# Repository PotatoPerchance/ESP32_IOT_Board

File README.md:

# ESP IoT Board

Custom-built 4-layer PCB IoT development board featuring onboard sensors for weather, ambient light, and audio processing, along with display support and integrated Wi-Fi/Bluetooth capabilities.

---

## Features

* **Sensors**: Temperature, humidity, pressure (BME280), and ambient light sensing.
* **Audio**: Microphone input with MAX4466EXK amplifier circuit.
* **Connectivity**: Integrated Wi-Fi and Bluetooth via ESP32-C3.
* **Power & Charging**: Onboard LiPo battery charger circuit (MCP73871) with USB power path management.
* **Storage & Expansion**: External Flash memory (W25Q32JVSSIQ) and MicroSD card slot.
* **Display Support**: Display header interface for external screens.
* **Interface**: USB Serial communication and power/charging over USB.

---

## Motivation

I designed this to gain hands-on experience in 4-layer PCB design for complex and high-density PCBS.

---

## PCB Layout

### Signal Layers (F.Cu & B.Cu)

### Power & Ground Planes (In1.Cu & In2.Cu)

---

## Project Directory Structure

| Path / File | Description |
| :--- | :--- |
| `3D models/` | 3D models for components|
| `Footprints/` | KiCad footprints used in the project |
| `Pictures/` | Image assets and PCB screenshots|
| `production/` | Production files (Gerbers, drill files, assembly outputs) |
| `Symbols/` | Custom KiCad schematic symbol library |
| `ESP IOT dev board.kicad_pcb` | Main KiCad PCB layout file |
| `ESP IOT dev board.kicad_sch` | Root schematic file |
| `esp32.kicad_sch` | ESP32-C3 microcontroller schematic sheet |
| `sensors.kicad_sch` | Environmental and audio sensor schematic sheet |
| `user_interface.kicad_sch` | Display and user interface schematic sheet |
| `README.md` | Project documentation |

---

## Bill of Materials (BOM)
| Component | Description | Est. Unit Cost (USD) |
| :--- | :--- | :--- |
| **ESP32-C3-WROOM-02** | Wi-Fi & BLE Microcontroller Module | ~$4.00 |
| **BME280** | Temperature, Humidity, & Pressure Sensor | ~$2.50 |
| **Light Sensor (LDR / Phototransistor)** | Ambient Light Sensing | ~$0.40 |
| **MAX4466EXK+T** | Low-Noise Microphone Amplifier IC | ~$1.20 |
| **Electret Condenser Microphone** | 2-pin Audio Input | ~$1 |
| **Winbond W25Q32JVSSIQ** | 32M-bit (4MB) SPI Flash Memory | ~$0.50 |
| **MCP73871** | LiPo Battery Charger & Power Path Management IC | ~$1.80 |
| **MicroSD Card Holder** | Push-Push / Push-Pull Socket | ~$1 |
| **USB Type-C Connector** | 16-pin / 24-pin Surface Mount Connector | ~$0.35 |
| **LiPo Battery** | 3.7V Single Cell Lithium-Polymer Battery | ~$3.50 |
| **Miscellaneous Components** | Resistors, Capacitors, LEDs, LDO, Connectors | ~$5.00 |
| **PCB Manufacturing** | Custom 4-Layer PCB Fabrication | ~$8.00 |
| **Shipping Fees** | Component & PCB Shipping | ~$15.00 |
| **Total Estimated Cost** | *(Including Fabrication & Shipping)* | **~$45** |

---

~ built with love ❤️

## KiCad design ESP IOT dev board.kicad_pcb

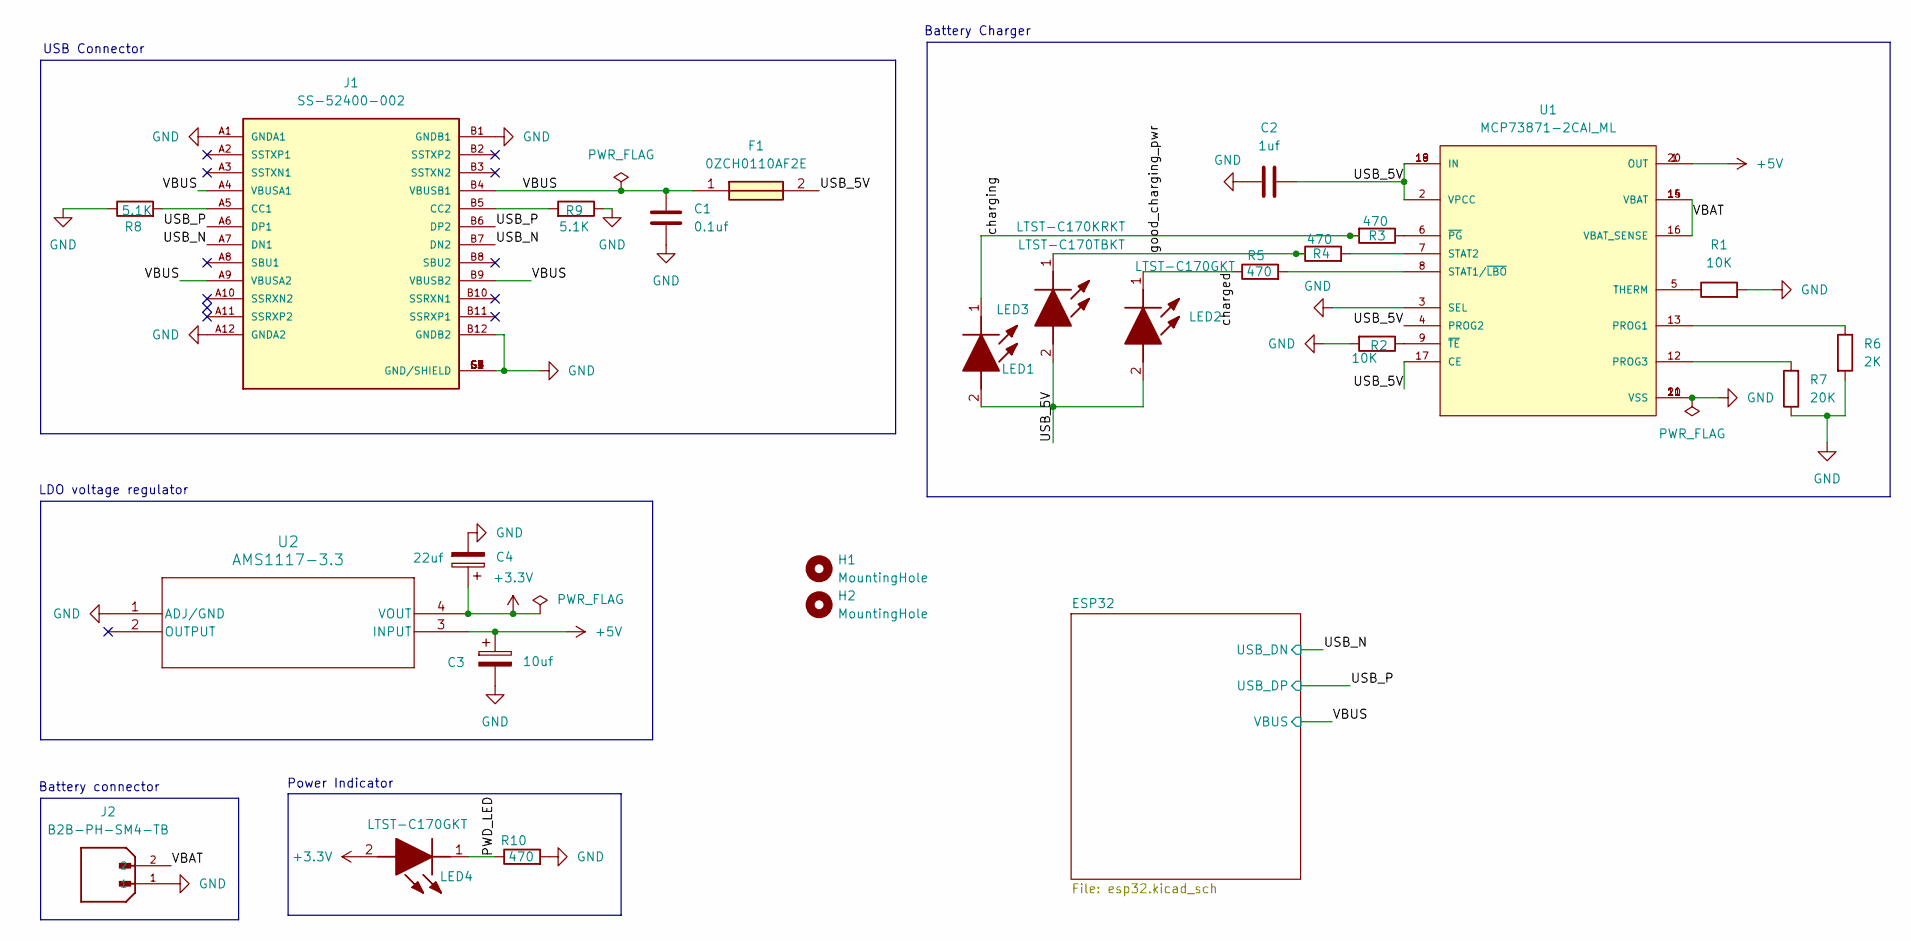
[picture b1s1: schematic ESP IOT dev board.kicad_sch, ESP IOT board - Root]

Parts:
C1: 0.1uf; C_0805_2012Metric_Pad1.18x1.45mm_HandSolder
C2: 1uf; C_0805_2012Metric_Pad1.18x1.45mm_HandSolder
C3: 10uf; CP_EIA-6032-28_Kemet-C_HandSolder
C4: 22uf; CP_EIA-6032-28_Kemet-C_HandSolder
F1: 0ZCH0110AF2E; FUSC3226X100N; Manufacturer_Part_Number 0ZCH0110AF2E
H1, H2: MountingHole; MountingHole_2.5mm
J1: SS-52400-002; BELFUSE_SS-52400-002; PARTREV A0
J2: B2B-PH-SM4-TB; JST_B2B-PH-SM4-TB; PARTREV N/A
LED1: LTST-C170KRKT; LEDC2012X120N; Manufacturer_Part_Number LTST-C170KRKT; Mouser Part Number 859-LTST-C170KRKT
LED2, LED4: LTST-C170GKT; LEDC2012X120N; Manufacturer_Part_Number LTST-C170GKT; Mouser Part Number 859-LTST-C170GKT
LED3: LTST-C170TBKT; LEDC2012X120N; Manufacturer_Part_Number LTST-C170TBKT; Mouser Part Number 859-LTST-C170TBKT
R1, R2: 10K; R_0805_2012Metric_Pad1.20x1.40mm_HandSolder
R3, R4, R5, R10: 470; R_0805_2012Metric_Pad1.20x1.40mm_HandSolder
R6: 2K; R_0805_2012Metric_Pad1.20x1.40mm_HandSolder
R7: 20K; R_0805_2012Metric_Pad1.20x1.40mm_HandSolder
R8, R9: 5.1K; R_0805_2012Metric_Pad1.20x1.40mm_HandSolder
U1: MCP73871-2CAI_ML; QFN50P400X400X100-21N; PARTREV D
U2: AMS1117-3.3; SOT_AMS1117-2.5_AMS

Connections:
+3.3V: C4.1, LED4.2 (A), U2.4 (VOUT); also elsewhere on the board
+5V: C3.1, U1.1 (OUT), U1.20 (OUT), U2.3 (INPUT)
/PWD_LED: LED4.1 (K), R10.1; also elsewhere on the board
/USB_5V: C2.2, F1.2, LED1.2 (A), LED2.2 (A), LED3.2 (A), U1.2 (VPCC), U1.4 (PROG2), U1.17 (CE), U1.18 (IN), U1.19 (IN); also elsewhere on the board
/USB_N: J1.A7 (DN1), J1.B7 (DN2); also elsewhere on the board
/USB_P: J1.A6 (DP1), J1.B6 (DP2); also elsewhere on the board
/VBAT: J2.2, U1.14 (VBAT), U1.15 (VBAT), U1.16 (VBAT_SENSE)
/VBUS: C1.1, F1.1, J1.A4 (VBUSA1), J1.A9 (VBUSA2), J1.B4 (VBUSB1), J1.B9 (VBUSB2); also elsewhere on the board
/charged: LED2.1 (K), R5.1; also elsewhere on the board
/charging: LED1.1 (K), R3.2; also elsewhere on the board
/good_charging_pwr: LED3.1 (K), R4.1; also elsewhere on the board
unnamed: J1.A5 (CC1), R8.2
unnamed: R6.1, U1.13 (PROG1)
unnamed: R7.2, U1.12 (PROG3)
unnamed: R5.2, U1.8 (STAT1/~LBO)
unnamed: R4.2, U1.7 (STAT2)
unnamed: R1.1, U1.5 (THERM)
unnamed: R3.1, U1.6 (~PG)
unnamed: R2.1, U1.9 (~TE)

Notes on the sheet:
LDO voltage regulator
Battery Charger
USB Connector
Battery connector
Power Indicator

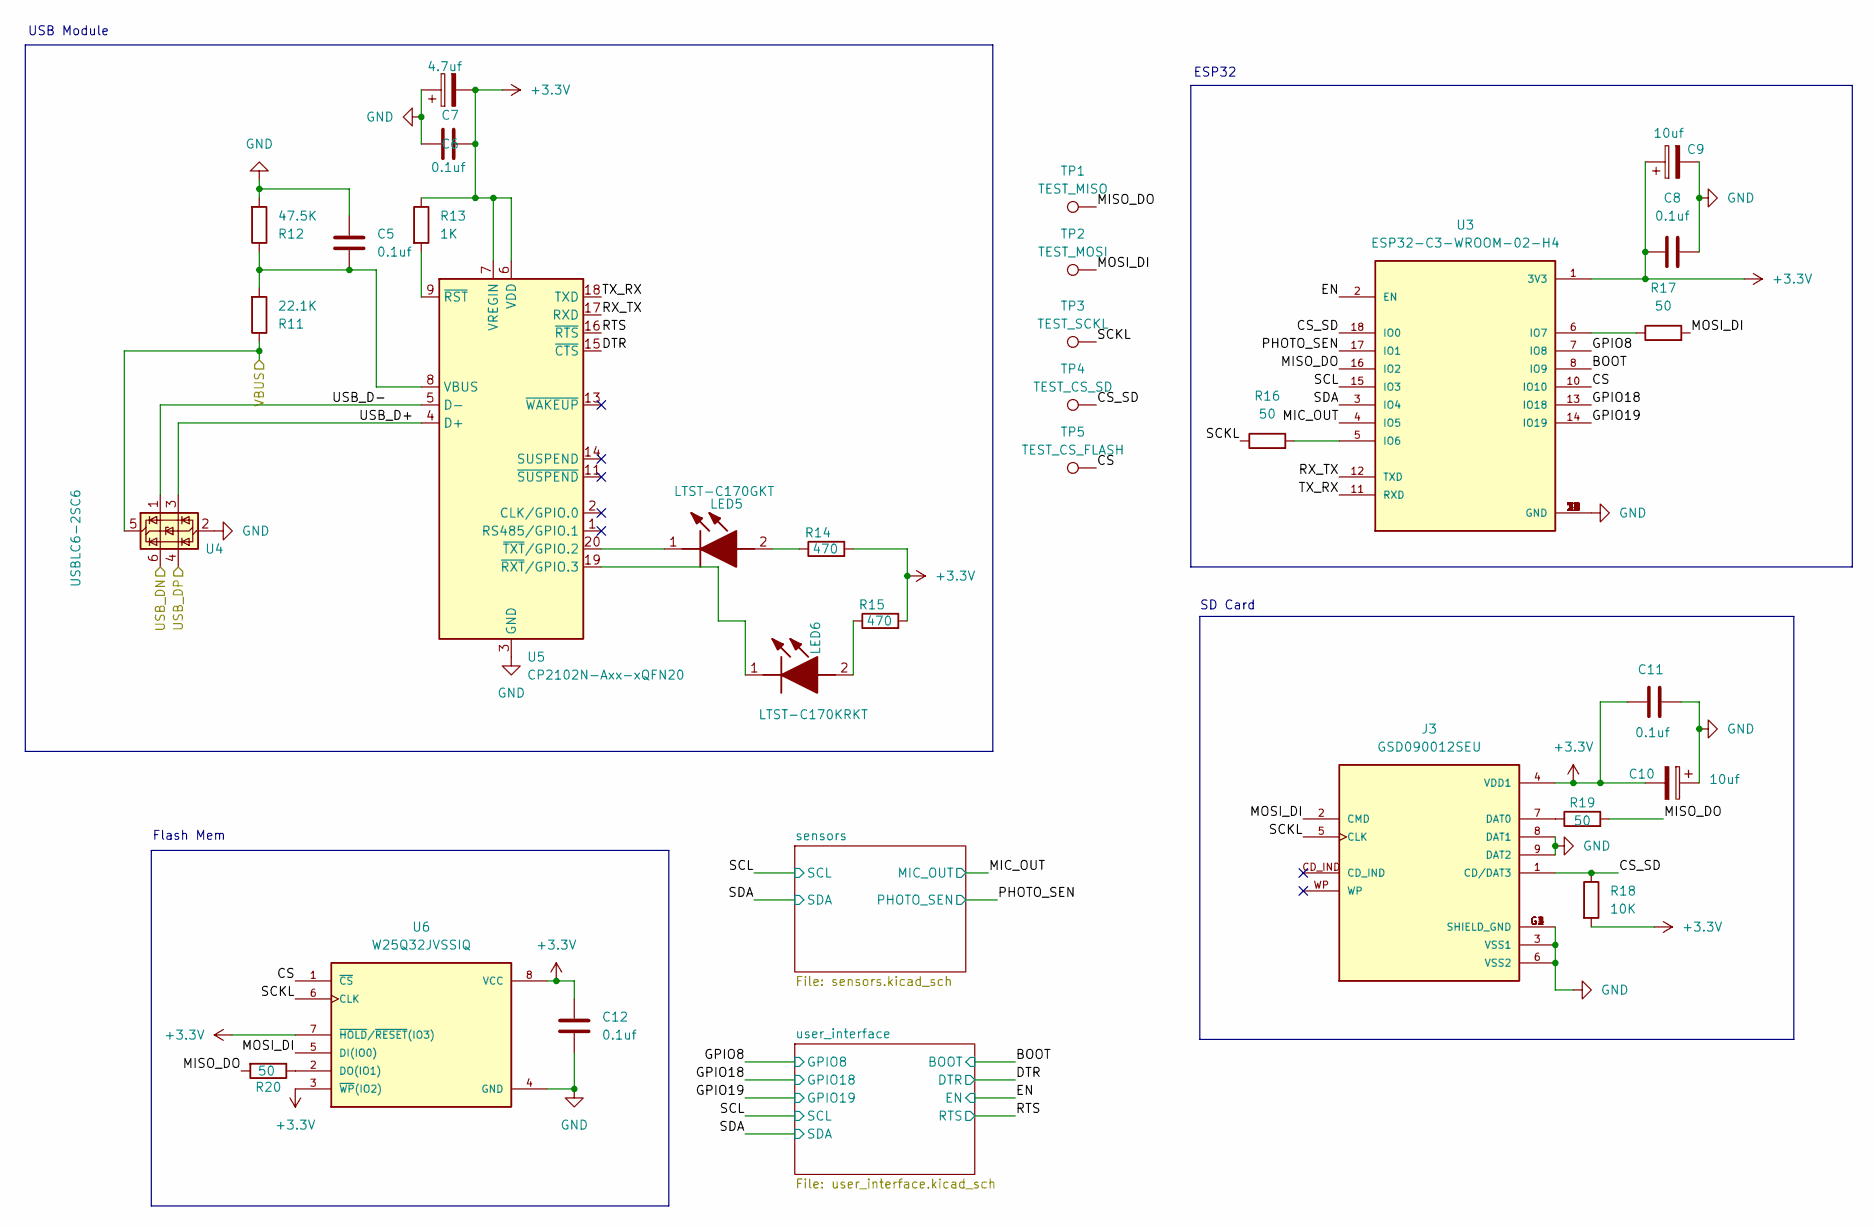
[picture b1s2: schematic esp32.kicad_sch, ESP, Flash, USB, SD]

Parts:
C5, C6, C8, C11, C12: 0.1uf; C_0805_2012Metric_Pad1.18x1.45mm_HandSolder
C7: 4.7uf; CP_EIA-6032-28_Kemet-C_HandSolder
C9, C10: 10uf; CP_EIA-6032-28_Kemet-C_HandSolder
J3: GSD090012SEU; AMPHENOL_GSD090012SEU; PARTREV E
LED5: LTST-C170GKT; LEDC2012X120N; Manufacturer_Part_Number LTST-C170GKT; Mouser Part Number 859-LTST-C170GKT
LED6: LTST-C170KRKT; LEDC2012X120N; Manufacturer_Part_Number LTST-C170KRKT; Mouser Part Number 859-LTST-C170KRKT
R11: 22.1K; R_0805_2012Metric_Pad1.20x1.40mm_HandSolder
R12: 47.5K; R_0805_2012Metric_Pad1.20x1.40mm_HandSolder
R13: 1K; R_0805_2012Metric_Pad1.20x1.40mm_HandSolder
R14, R15: 470; R_0805_2012Metric_Pad1.20x1.40mm_HandSolder
R16, R17, R19, R20: 50; R_0805_2012Metric_Pad1.20x1.40mm_HandSolder
R18: 10K; R_0805_2012Metric_Pad1.20x1.40mm_HandSolder
TP1: TEST_MISO; TestPoint_Pad_D1.0mm
TP2: TEST_MOSI; TestPoint_Pad_D1.0mm
TP3: TEST_SCKL; TestPoint_Pad_D1.0mm
TP4: TEST_CS_SD; TestPoint_Pad_D1.0mm
TP5: TEST_CS_FLASH; TestPoint_Pad_D1.0mm
U3: ESP32-C3-WROOM-02-H4; MODULE_ESP32-C3-WROOM-02-H4
U4: USBLC6-2SC6; SOT-23-6
U5: CP2102N-Axx-xQFN20; SiliconLabs_QFN-20-1EP_3x3mm_P0.5mm_EP1.8x1.8mm
U6: W25Q32JVSSIQ; SOIC127P790X216-8N; M_PART_NUMBER W25QXX

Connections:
+3.3V: C6.2, C7.2, C8.1, C9.1, C10.2, C11.2, C12.2, J3.4 (VDD1), R13.1, R14.2, R15.2, R18.2, U3.1 (3V3), U5.6 (VDD), U5.7 (VREGIN), U6.3 (~WP(IO2)), U6.7 (~HOLD/~RESET(IO3)), U6.8 (VCC); also elsewhere on the board
/ESP32/BOOT: U3.8 (IO9); also elsewhere on the board
/ESP32/CS: TP5.1 (1_1), U3.10 (IO10), U6.1 (~CS)
/ESP32/CS_SD: J3.1 (CD/DAT3), R18.1, TP4.1 (1_1), U3.18 (IO0)
/ESP32/DTR: U5.15 (~CTS); also elsewhere on the board
/ESP32/EN: U3.2 (EN); also elsewhere on the board
/ESP32/GPIO8: U3.7 (IO8); also elsewhere on the board
/ESP32/GPIO18: U3.13 (IO18); also elsewhere on the board
/ESP32/GPIO19: U3.14 (IO19); also elsewhere on the board
/ESP32/MIC_OUT: U3.4 (IO5); also elsewhere on the board
/ESP32/MISO_DO: R19.2, R20.2, TP1.1 (1_1), U3.16 (IO2)
/ESP32/MOSI_DI: J3.2 (CMD), R17.2, TP2.1 (1_1), U6.5 (DI(IO0))
/ESP32/PHOTO_SEN: U3.17 (IO1); also elsewhere on the board
/ESP32/RTS: U5.16 (~RTS); also elsewhere on the board
/ESP32/RX_TX: U3.12 (TXD), U5.17 (RXD)
/ESP32/SCKL: J3.5 (CLK), R16.1, TP3.1 (1_1), U6.6 (CLK)
/ESP32/SCL: U3.15 (IO3); also elsewhere on the board
/ESP32/SDA: U3.3 (IO4); also elsewhere on the board
/ESP32/TX_RX: U3.11 (RXD), U5.18 (TXD)
/ESP32/USB_D+: U4.3 (I/O2), U5.4 (D+)
/ESP32/USB_D-: U4.1 (I/O1), U5.5 (D-)
/USB_N: U4.6 (I/O1); also elsewhere on the board
/USB_P: U4.4 (I/O2); also elsewhere on the board
/VBUS: R11.1, U4.5 (VBUS); also elsewhere on the board
unnamed: J3.7 (DAT0), R19.1
unnamed: LED5.2 (A), R14.1
unnamed: LED5.1 (K), U5.20 (~TXT/GPIO.2)
unnamed: LED6.2 (A), R15.1
unnamed: LED6.1 (K), U5.19 (~RXT/GPIO.3)
unnamed: R16.2, U3.5 (IO6)
unnamed: R17.1, U3.6 (IO7)
unnamed: C5.2, R11.2, R12.1, U5.8 (VBUS)
unnamed: R13.2, U5.9 (~RST)
unnamed: R20.1, U6.2 (DO(IO1))

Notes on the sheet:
Flash Mem
SD Card
ESP32
USB Module

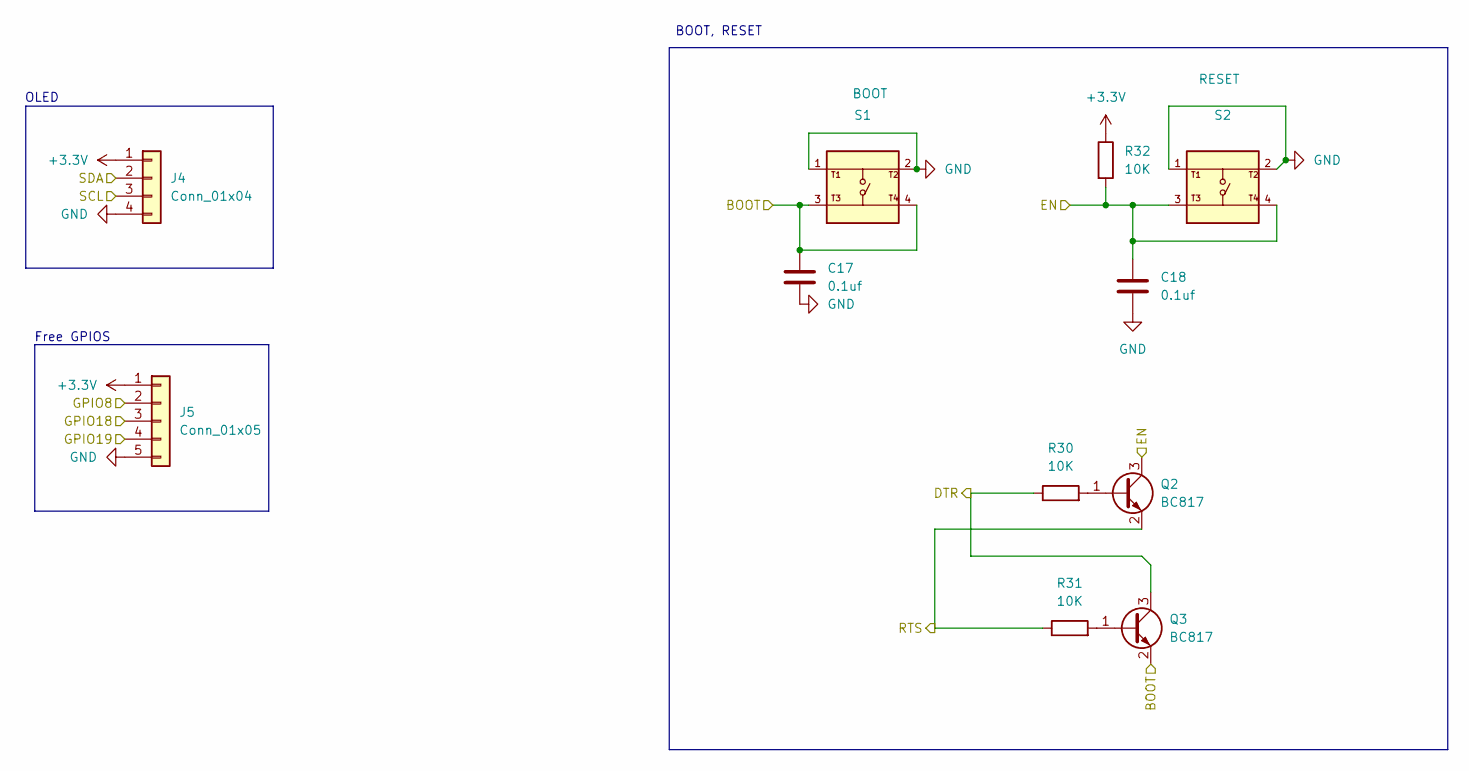
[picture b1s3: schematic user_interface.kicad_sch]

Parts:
C17, C18: 0.1uf; C_0805_2012Metric_Pad1.18x1.45mm_HandSolder
J4: Conn_01x04; PinHeader_1x04_P2.54mm_Vertical
J5: Conn_01x05; PinHeader_1x05_P2.54mm_Vertical
Q2, Q3: BC817; SOT-23
R30, R31, R32: 10K; R_0805_2012Metric_Pad1.20x1.40mm_HandSolder
S1: BOOT; SW_USLPT2819DT2TR; PARTREV P
S2: RESET; SW_USLPT2819DT2TR; PARTREV P

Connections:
+3.3V: J4.1, J5.1, R32.1; also elsewhere on the board
/ESP32/BOOT: C17.1, Q3.2 (E), S1.3, S1.4; also elsewhere on the board
/ESP32/DTR: Q3.3 (C), R30.1; also elsewhere on the board
/ESP32/EN: C18.1, Q2.3 (C), R32.2, S2.3, S2.4; also elsewhere on the board
/ESP32/GPIO8: J5.2; also elsewhere on the board
/ESP32/GPIO18: J5.3; also elsewhere on the board
/ESP32/GPIO19: J5.4; also elsewhere on the board
/ESP32/RTS: Q2.2 (E), R31.1; also elsewhere on the board
/ESP32/SCL: J4.3; also elsewhere on the board
/ESP32/SDA: J4.2; also elsewhere on the board
unnamed: Q2.1 (B), R30.2
unnamed: Q3.1 (B), R31.2

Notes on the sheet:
BOOT, RESET
Free GPIOS
OLED

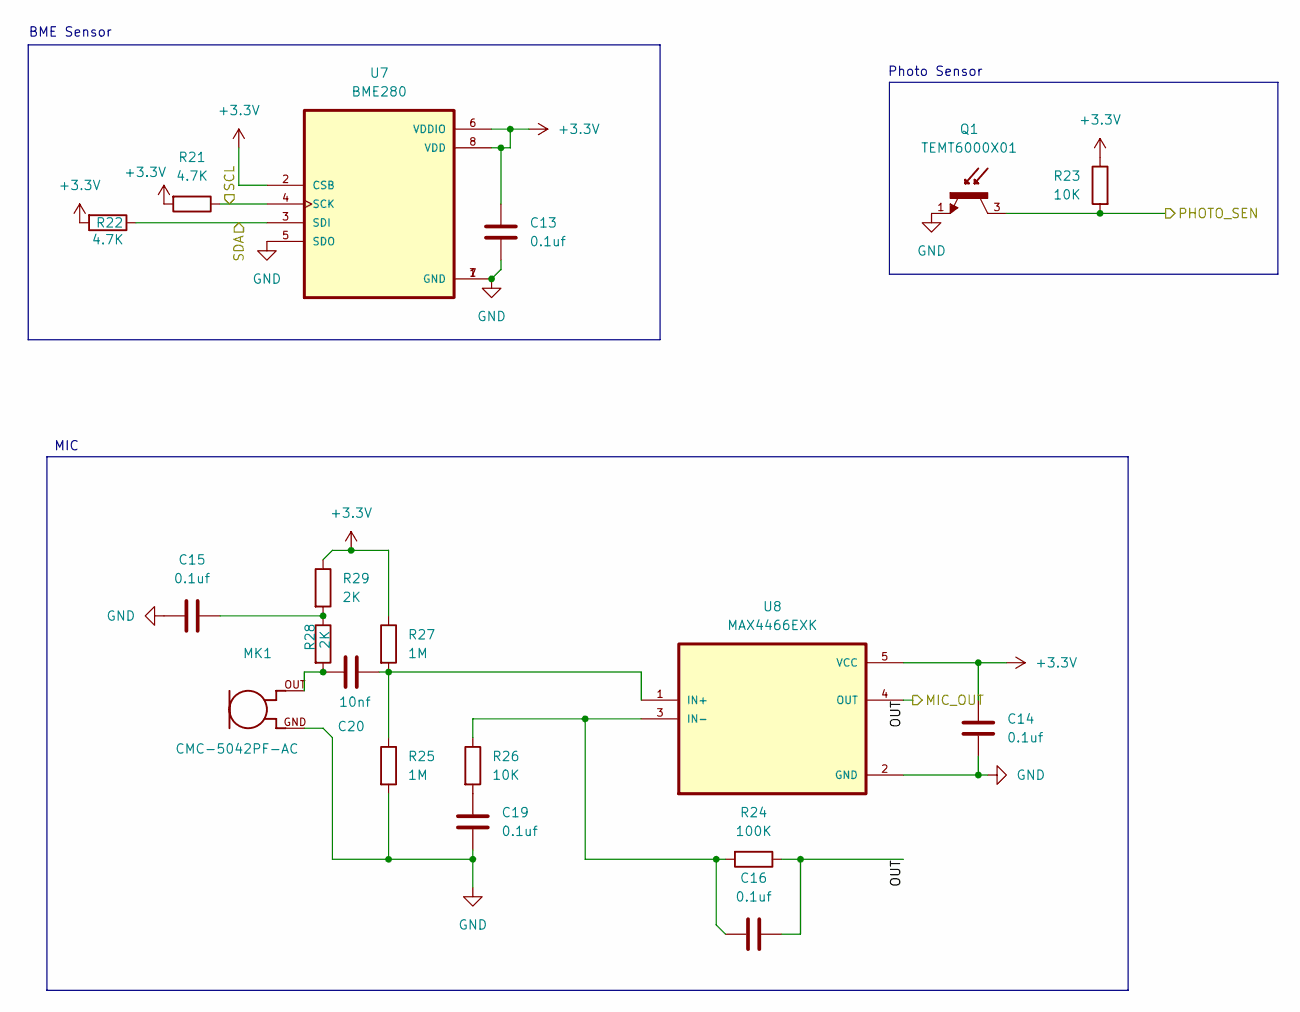
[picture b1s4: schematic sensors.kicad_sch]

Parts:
C13, C14, C15, C16, C19: 0.1uf; C_0805_2012Metric_Pad1.18x1.45mm_HandSolder
C20: 10nf; C_0805_2012Metric_Pad1.18x1.45mm_HandSolder
MK1: CMC-5042PF-AC; CUI_CMC-5042PF-AC
Q1: TEMT6000X01; TRANS_TEMT6000X01; PARTREV 1.9
R21, R22: 4.7K; R_0805_2012Metric_Pad1.20x1.40mm_HandSolder
R23, R26: 10K; R_0805_2012Metric_Pad1.20x1.40mm_HandSolder
R24: 100K; R_0805_2012Metric_Pad1.20x1.40mm_HandSolder
R25, R27: 1M; R_0805_2012Metric_Pad1.20x1.40mm_HandSolder
R28, R29: 2K; R_0805_2012Metric_Pad1.20x1.40mm_HandSolder
U7: BME280; PSON65P250X250X100-8N
U8: MAX4466EXK; SOT65P210X110-5N

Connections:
+3.3V: C13.1, C14.1, R21.2, R22.2, R23.1, R27.1, R29.1, U7.2 (CSB), U7.6 (VDDIO), U7.8 (VDD), U8.5 (VCC); also elsewhere on the board
/ESP32/MIC_OUT: C16.2, R24.1, U8.4 (OUT); also elsewhere on the board
/ESP32/PHOTO_SEN: Q1.3, R23.2; also elsewhere on the board
/ESP32/SCL: R21.1, U7.4 (SCK); also elsewhere on the board
/ESP32/SDA: R22.1, U7.3 (SDI); also elsewhere on the board
unnamed: C15.2, R28.1, R29.2
unnamed: C19.2, R26.2
unnamed: C20.2, MK1.OUT, R28.2
unnamed: C20.1, R25.1, R27.2, U8.1 (IN+)
unnamed: C16.1, R24.2, R26.1, U8.3 (IN-)

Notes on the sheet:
Photo Sensor
MIC
BME Sensor

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
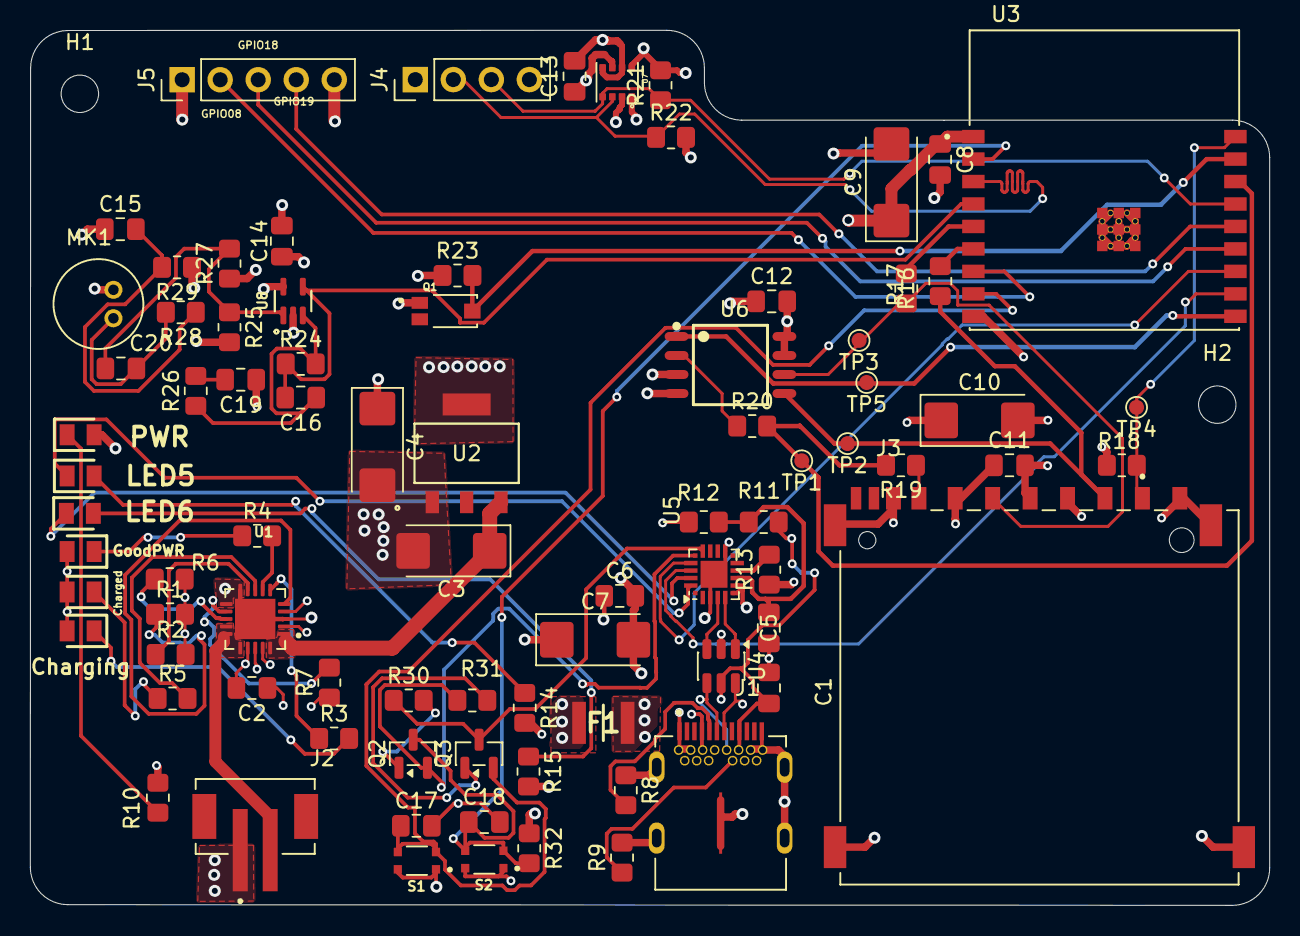
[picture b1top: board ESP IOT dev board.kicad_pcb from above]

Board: 4 copper layers, 82.8 x 58.4 mm, 85 parts (0 on the bottom side), 58 nets.

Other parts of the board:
Charged: LTST-C170GKT; LEDC2012X120N
Charging: LTST-C170KRKT; LEDC2012X120N
GoodPWR: LTST-C170TBKT; LEDC2012X120N
PWR: LTST-C170GKT; LEDC2012X120N

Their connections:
+3.3V: PWR.2 (A); also elsewhere on the board
/PWD_LED: PWR.1 (K); also elsewhere on the board
/USB_5V: Charged.2 (A), Charging.2 (A), GoodPWR.2 (A); also elsewhere on the board
/charged: Charged.1 (K); also elsewhere on the board
/charging: Charging.1 (K); also elsewhere on the board
/good_charging_pwr: GoodPWR.1 (K); also elsewhere on the board

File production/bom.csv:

Designator,Footprint,Quantity,Value,LCSC Part #
"C1, C11, C12, C13, C14, C15, C16, C17, C18, C19, C5, C6, C8",0805,13,0.1uf,
"C10, C3, C9",CP_EIA-6032-28_Kemet-C_HandSolder,3,10uf,
C2,0805,1,1uf,
C20,0805,1,10nf,
C4,CP_EIA-6032-28_Kemet-C_HandSolder,1,22uf,
C7,CP_EIA-6032-28_Kemet-C_HandSolder,1,4.7uf,
"CHARGED, LED5, PWR",LEDC2012X120N,3,LTST-C170GKT,
"CHARGING, LED6",LEDC2012X120N,2,LTST-C170KRKT,
F1,FUSC3226X100N,1,0ZCH0110AF2E,
GOODPWR,LEDC2012X120N,1,LTST-C170TBKT,
J1,BELFUSE_SS-52400-002,1,SS-52400-002,
J2,JST_B2B-PH-SM4-TB,1,B2B-PH-SM4-TB,
J3,AMPHENOL_GSD090012SEU,1,GSD090012SEU,
J4,PinHeader_1x04_P2.54mm_Vertical,1,Conn_01x04,
J5,PinHeader_1x05_P2.54mm_Vertical,1,Conn_01x05,
MK1,CUI_CMC-5042PF-AC,1,CMC-5042PF-AC,
Q1,TRANS_TEMT6000X01,1,TEMT6000X01,
"Q2, Q3",SOT-23,2,BC817,
"R1, R18, R2, R23, R26, R30, R31, R32",0805,8,10K,
"R10, R14, R15, R3, R4, R5",0805,6,470,
R11,0805,1,22.1K,
R12,0805,1,47.5K,
R13,0805,1,1K,
"R16, R17, R19, R20",0805,4,50,
"R21, R22",0805,2,4.7K,
R24,0805,1,100K,
"R25, R27",0805,2,1M,
"R28, R29, R6",0805,3,2K,
R7,0805,1,20K,
"R8, R9",0805,2,5.1K,
S1,SW_USLPT2819DT2TR,1,BOOT,
S2,SW_USLPT2819DT2TR,1,RESET,
TP1,TestPoint_Pad_D1.0mm,1,TEST_MISO,
TP2,TestPoint_Pad_D1.0mm,1,TEST_MOSI,
TP3,TestPoint_Pad_D1.0mm,1,TEST_SCKL,
TP4,TestPoint_Pad_D1.0mm,1,TEST_CS_SD,
TP5,TestPoint_Pad_D1.0mm,1,TEST_CS_FLASH,
U1,QFN50P400X400X100-21N,1,MCP73871-2CAI_ML,
U2,SOT_AMS1117-2.5_AMS,1,AMS1117-3.3,
U3,MODULE_ESP32-C3-WROOM-02-H4,1,ESP32-C3-WROOM-02-H4,
U4,SOT-23-6,1,USBLC6-2SC6,
U5,SiliconLabs_QFN-20-1EP_3x3mm_P0.5mm_EP1.8x1.8mm,1,CP2102N-Axx-xQFN20,
U6,SOIC127P790X216-8N,1,W25Q32JVSSIQ,
U7,PSON65P250X250X100-8N,1,BME280,
U8,SOT65P210X110-5N,1,MAX4466EXK,
